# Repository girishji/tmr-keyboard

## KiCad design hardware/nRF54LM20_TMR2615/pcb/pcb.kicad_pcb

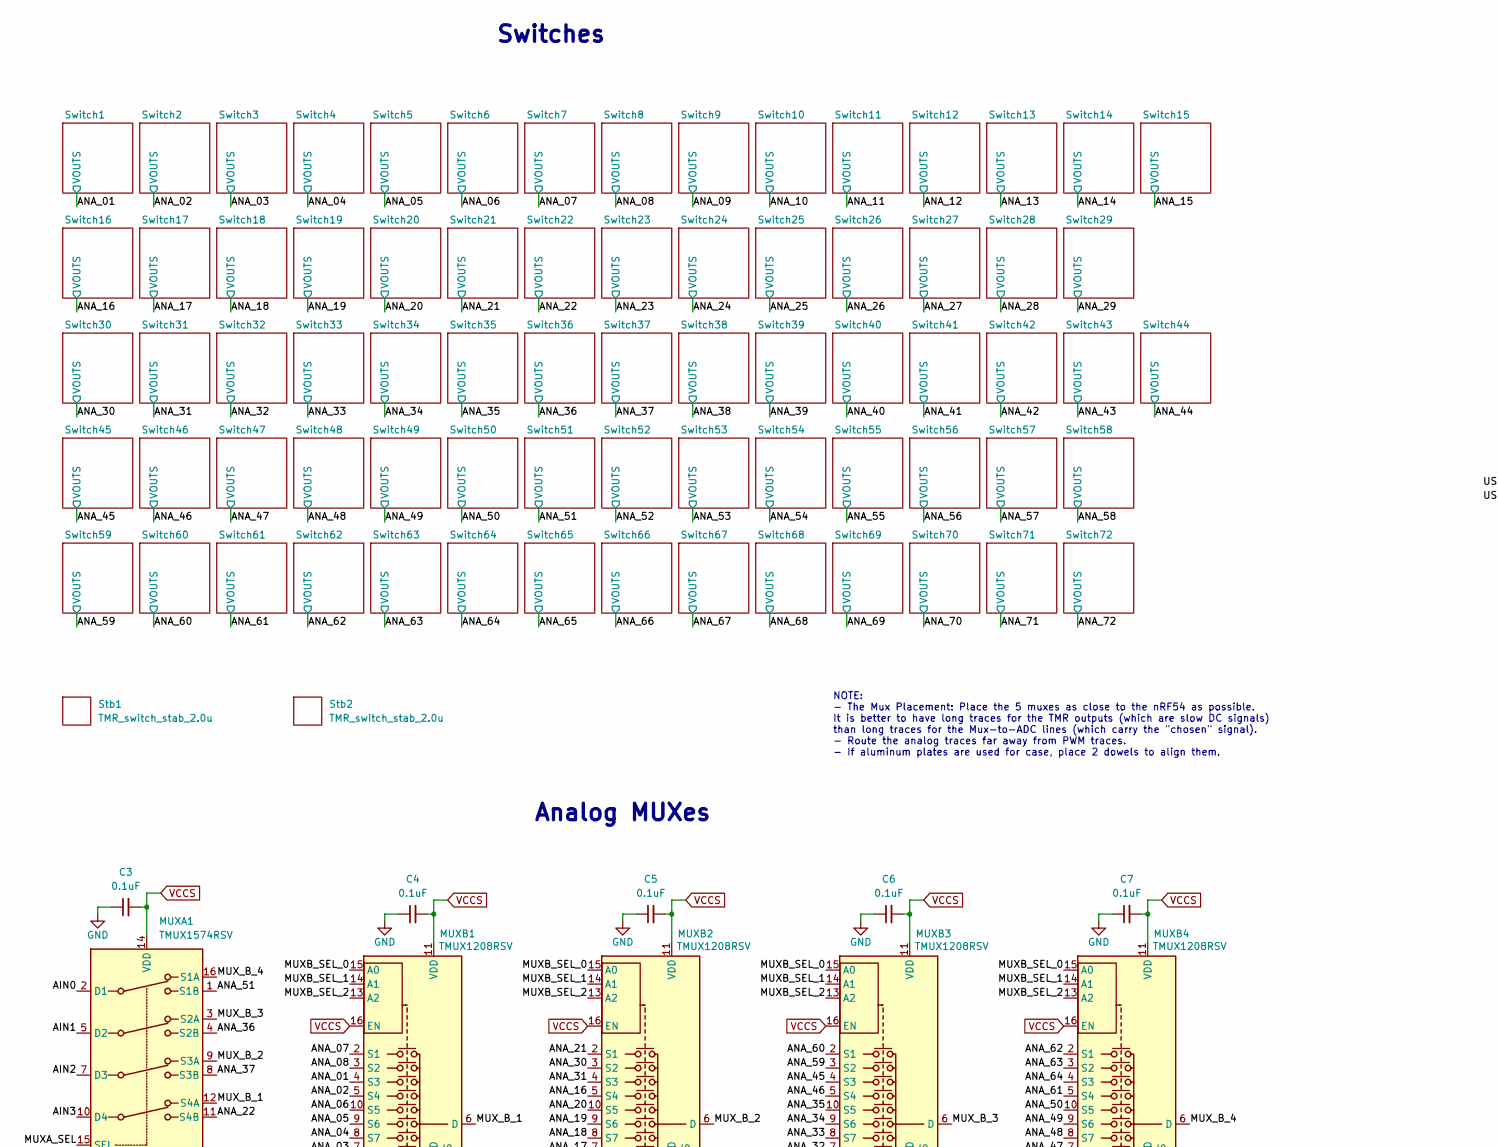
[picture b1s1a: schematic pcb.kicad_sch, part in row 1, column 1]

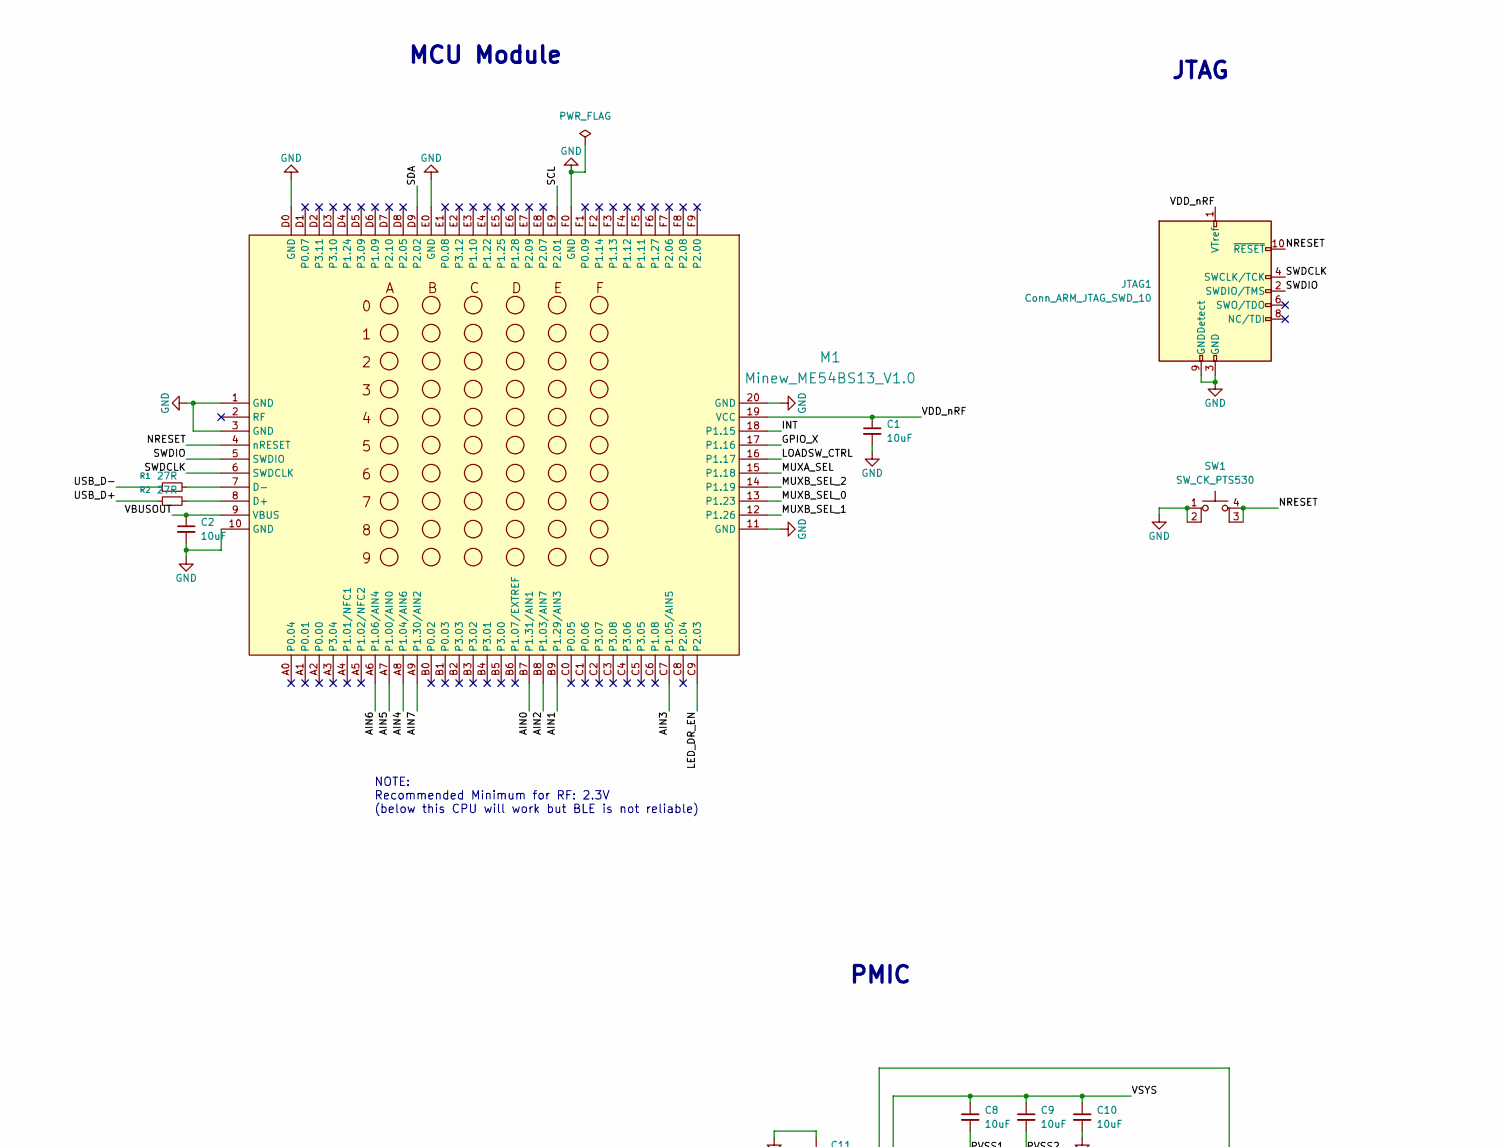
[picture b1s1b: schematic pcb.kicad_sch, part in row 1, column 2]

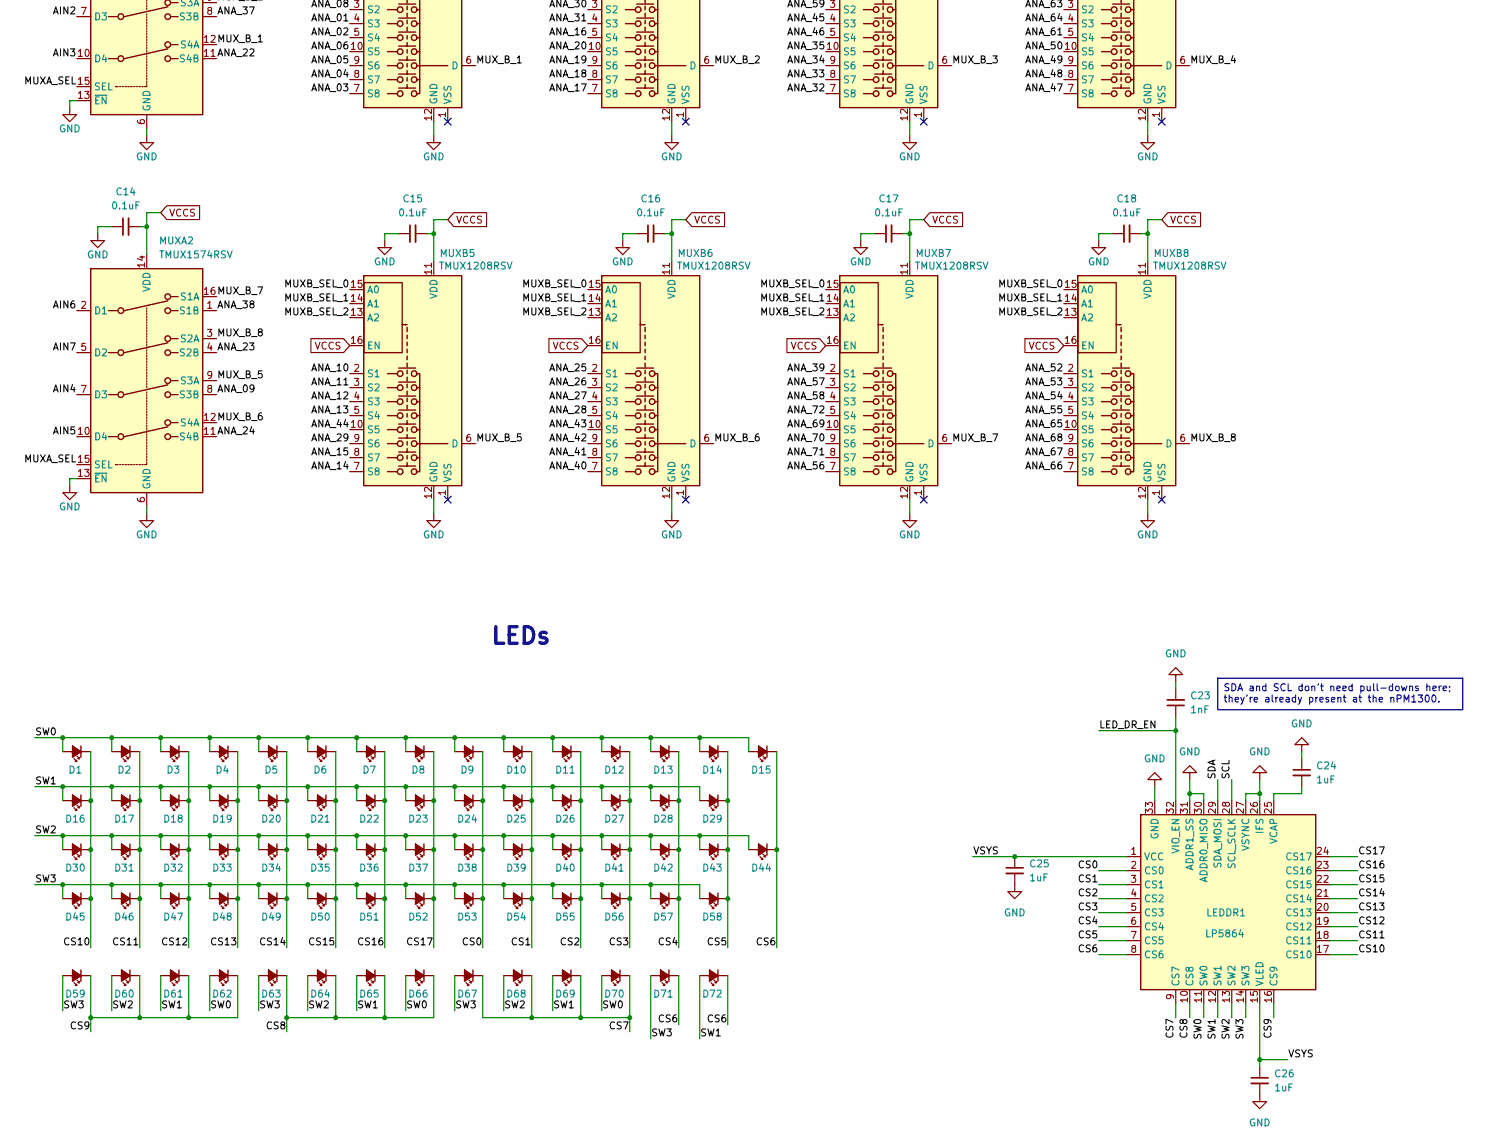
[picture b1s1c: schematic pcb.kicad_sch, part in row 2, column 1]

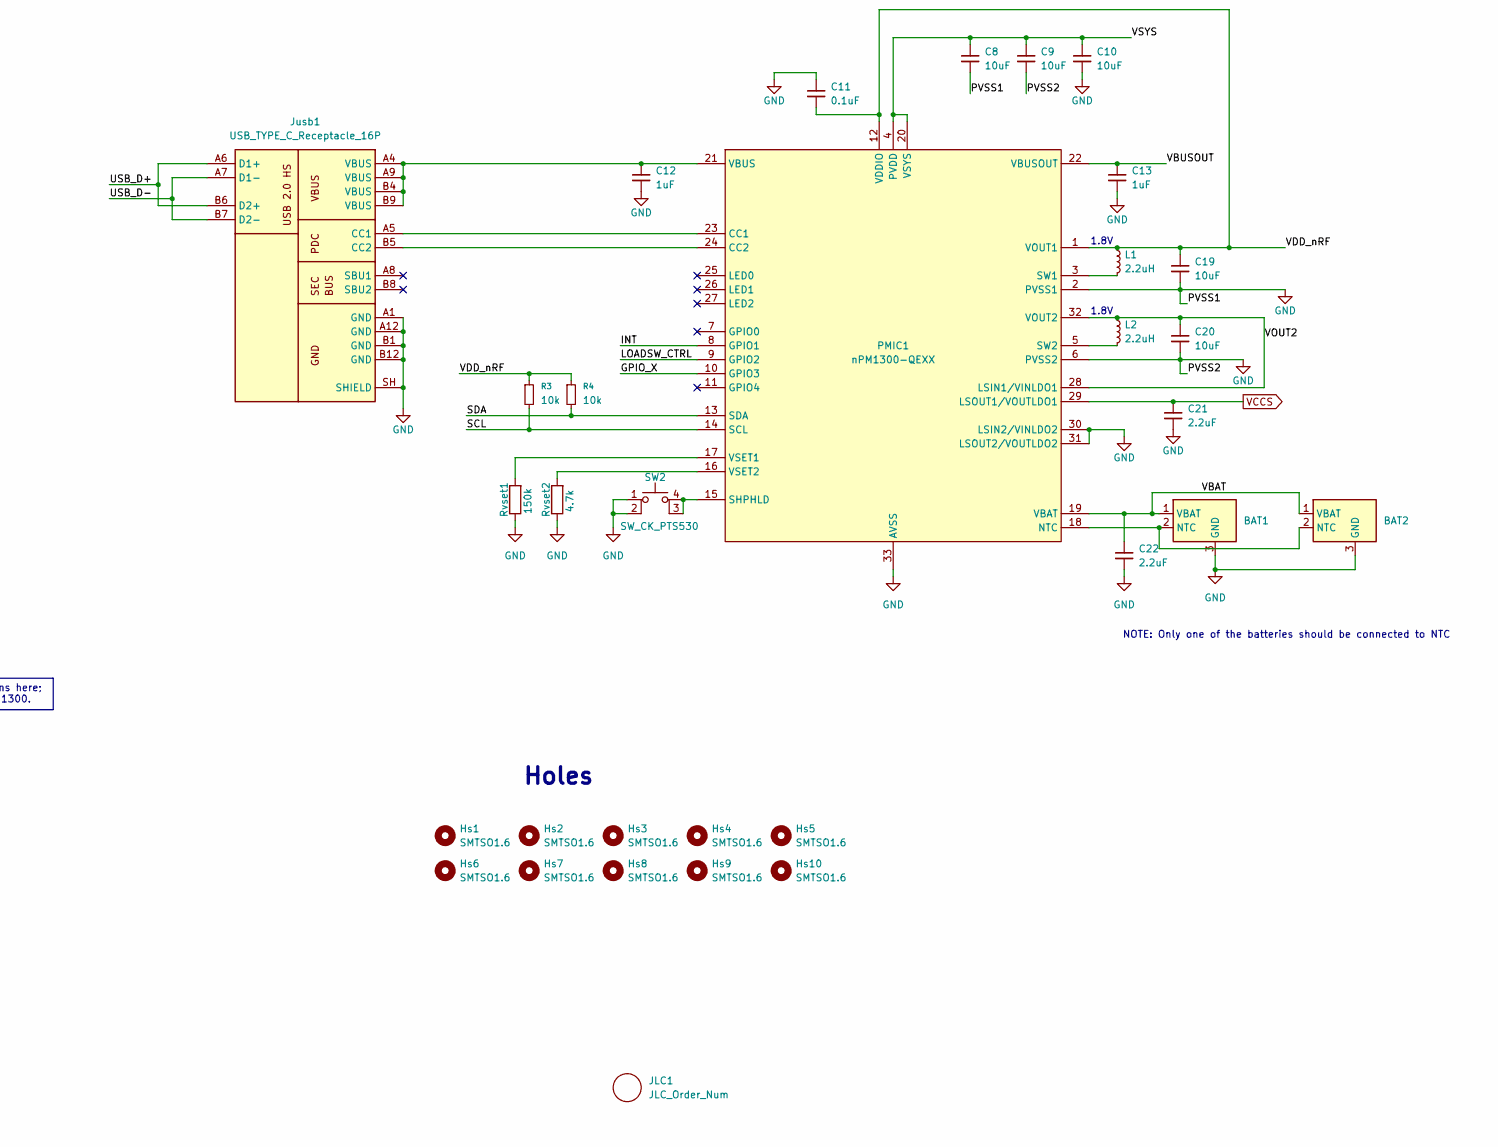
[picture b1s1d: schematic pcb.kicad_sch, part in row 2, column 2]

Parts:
BAT1, BAT2: PCB_Wire_Solder_3p_Connector
C1, C2, C8, C9, C10, C19, C20: 10uF; C_0603_1608Metric; LCSC C96446
C3, C4, C5, C6, C7, C11, C14, C15, C16, C17, C18: 0.1uF; C_0402_1005Metric; LCSC C129131
C12, C13, C24, C25, C26: 1uF; C_0402_1005Metric; LCSC C14445
C21, C22: 2.2uF; C_0603_1608Metric; LCSC C57895
C23: 1nF; C_0402_1005Metric; LCSC C710873
D1, D2, D3, D4, D5, D6, D7, D8, D9, D10, D11, D12, D13, D14, D15, D16, D17, D18, D19, D20, D21, D22, D23, D24, D25, D26, D27, D28, D29, D30, D31, D32, D33, D34, D35, D36, D37, D38, D39, D40, D41, D42, D43, D44, D45, D46, D47, D48, D49, D50, D51, D52, D53, D54, D55, D56, D57, D58, D59, D60, D61, D62, D63, D64, D65, D66, D67, D68, D69, D70, D71, D72: LED; LED_1206_3216Metric_ReverseMount_Hole2.1mm; LCSC C401114
Hs1, Hs2, Hs3, Hs4, Hs5, Hs6, Hs7, Hs8, Hs9, Hs10: SMTSO1.6; SMTSO_M1.6; LCSC C42924166
JLC1: JLC_Order_Num
JTAG1: Conn_ARM_JTAG_SWD_10; SAMTEC-CLP-105-02-X-D-A; LCSC C6882278
Jusb1: USB_TYPE_C_Receptacle_16P; USB_C_Receptacle_XKB_U262-16XN-4BVC11; MPN U262-161N-4BVC11; LCSC C319148
L1, L2: 2.2uH; L_Samsung_CIGT201610EH2R2MNE; LCSC C2049745
LEDDR1: LP5864; LP5864-VQFN-32-1EP_4x4mm_P0.4mm_EP2.8x2.8mm_ThermalVias; LCSC C5220564
M1: Minew_ME54BS13_V1.0; Minew_ME54BS13; LCSC C9900300294
MUXA1, MUXA2: TMUX1574RSV; UQFN-16_1.8x2.6mm_P0.4mm; LCSC C2673120
MUXB1, MUXB2, MUXB3, MUXB4, MUXB5, MUXB6, MUXB7, MUXB8: TMUX1208RSV; UQFN-16_1.8x2.6mm_P0.4mm; LCSC C2673274
PMIC1: nPM1300-QEXX; QFN-32-1EP_5x5mm_P0.5mm_EP3.6x3.6mm_ThermalVias; LCSC C25346894
R1, R2: 27R; R_0402_1005Metric; LCSC C25100
R3, R4: 10k; R_0402_1005Metric; LCSC C25744
Rvset1: 150k; R_0402_1005Metric; LCSC C25755
Rvset2: 4.7k; R_0402_1005Metric; LCSC C25900
SW1, SW2: SW_CK_PTS530; SW_CK_PTS530_4.5x4.5x0.55mm; LCSC C221860
Stb1, Stb2: TMR_switch_stab_2.0u; Stabilizer_Lowpro_2U

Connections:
/AIN0: M1.B7 (P1.31/AIN1), MUXA1.2 (D1)
/AIN1: M1.B9 (P1.29/AIN3), MUXA1.5 (D2)
/AIN2: M1.B8 (P1.03/AIN7), MUXA1.7 (D3)
/AIN3: M1.C7 (P1.05/AIN5), MUXA1.10 (D4)
/AIN4: M1.A8 (P1.04/AIN6), MUXA2.7 (D3)
/AIN5: M1.A7 (P1.00/AIN0), MUXA2.10 (D4)
/AIN6: M1.A6 (P1.06/AIN4), MUXA2.2 (D1)
/AIN7: M1.A9 (P1.30/AIN2), MUXA2.5 (D2)
/ANA_01: MUXB1.4 (S3); also elsewhere on the board
/ANA_02: MUXB1.5 (S4); also elsewhere on the board
/ANA_03: MUXB1.7 (S8); also elsewhere on the board
/ANA_04: MUXB1.8 (S7); also elsewhere on the board
/ANA_05: MUXB1.9 (S6); also elsewhere on the board
/ANA_06: MUXB1.10 (S5); also elsewhere on the board
/ANA_07: MUXB1.2 (S1); also elsewhere on the board
/ANA_08: MUXB1.3 (S2); also elsewhere on the board
/ANA_09: MUXA2.8 (S3B); also elsewhere on the board
/ANA_10: MUXB5.2 (S1); also elsewhere on the board
/ANA_11: MUXB5.3 (S2); also elsewhere on the board
/ANA_12: MUXB5.4 (S3); also elsewhere on the board
/ANA_13: MUXB5.5 (S4); also elsewhere on the board
/ANA_14: MUXB5.7 (S8); also elsewhere on the board
/ANA_15: MUXB5.8 (S7); also elsewhere on the board
/ANA_16: MUXB2.5 (S4); also elsewhere on the board
/ANA_17: MUXB2.7 (S8); also elsewhere on the board
/ANA_18: MUXB2.8 (S7); also elsewhere on the board
/ANA_19: MUXB2.9 (S6); also elsewhere on the board
/ANA_20: MUXB2.10 (S5); also elsewhere on the board
/ANA_21: MUXB2.2 (S1); also elsewhere on the board
/ANA_22: MUXA1.11 (S4B); also elsewhere on the board
/ANA_23: MUXA2.4 (S2B); also elsewhere on the board
/ANA_24: MUXA2.11 (S4B); also elsewhere on the board
/ANA_25: MUXB6.2 (S1); also elsewhere on the board
/ANA_26: MUXB6.3 (S2); also elsewhere on the board
/ANA_27: MUXB6.4 (S3); also elsewhere on the board
/ANA_28: MUXB6.5 (S4); also elsewhere on the board
/ANA_29: MUXB5.9 (S6); also elsewhere on the board
/ANA_30: MUXB2.3 (S2); also elsewhere on the board
/ANA_31: MUXB2.4 (S3); also elsewhere on the board
/ANA_32: MUXB3.7 (S8); also elsewhere on the board
/ANA_33: MUXB3.8 (S7); also elsewhere on the board
/ANA_34: MUXB3.9 (S6); also elsewhere on the board
/ANA_35: MUXB3.10 (S5); also elsewhere on the board
/ANA_36: MUXA1.4 (S2B); also elsewhere on the board
/ANA_37: MUXA1.8 (S3B); also elsewhere on the board
/ANA_38: MUXA2.1 (S1B); also elsewhere on the board
/ANA_39: MUXB7.2 (S1); also elsewhere on the board
/ANA_40: MUXB6.7 (S8); also elsewhere on the board
/ANA_41: MUXB6.8 (S7); also elsewhere on the board
/ANA_42: MUXB6.9 (S6); also elsewhere on the board
/ANA_43: MUXB6.10 (S5); also elsewhere on the board
/ANA_44: MUXB5.10 (S5); also elsewhere on the board
/ANA_45: MUXB3.4 (S3); also elsewhere on the board
/ANA_46: MUXB3.5 (S4); also elsewhere on the board
/ANA_47: MUXB4.7 (S8); also elsewhere on the board
/ANA_48: MUXB4.8 (S7); also elsewhere on the board
/ANA_49: MUXB4.9 (S6); also elsewhere on the board
/ANA_50: MUXB4.10 (S5); also elsewhere on the board
/ANA_51: MUXA1.1 (S1B); also elsewhere on the board
/ANA_52: MUXB8.2 (S1); also elsewhere on the board
/ANA_53: MUXB8.3 (S2); also elsewhere on the board
/ANA_54: MUXB8.4 (S3); also elsewhere on the board
/ANA_55: MUXB8.5 (S4); also elsewhere on the board
/ANA_56: MUXB7.7 (S8); also elsewhere on the board
/ANA_57: MUXB7.3 (S2); also elsewhere on the board
/ANA_58: MUXB7.4 (S3); also elsewhere on the board
/ANA_59: MUXB3.3 (S2); also elsewhere on the board
/ANA_60: MUXB3.2 (S1); also elsewhere on the board
/ANA_61: MUXB4.5 (S4); also elsewhere on the board
/ANA_62: MUXB4.2 (S1); also elsewhere on the board
/ANA_63: MUXB4.3 (S2); also elsewhere on the board
/ANA_64: MUXB4.4 (S3); also elsewhere on the board
/ANA_65: MUXB8.10 (S5); also elsewhere on the board
/ANA_66: MUXB8.7 (S8); also elsewhere on the board
/ANA_67: MUXB8.8 (S7); also elsewhere on the board
/ANA_68: MUXB8.9 (S6); also elsewhere on the board
/ANA_69: MUXB7.10 (S5); also elsewhere on the board
/ANA_70: MUXB7.9 (S6); also elsewhere on the board
/ANA_71: MUXB7.8 (S7); also elsewhere on the board
/ANA_72: MUXB7.5 (S4); also elsewhere on the board
/CS0: D9.1 (K), D24.1 (K), D38.1 (K), D53.1 (K), LEDDR1.2 (CS0)
/CS1: D10.1 (K), D25.1 (K), D39.1 (K), D54.1 (K), LEDDR1.3 (CS1)
/CS2: D11.1 (K), D26.1 (K), D40.1 (K), D55.1 (K), LEDDR1.4 (CS2)
/CS3: D12.1 (K), D27.1 (K), D41.1 (K), D56.1 (K), LEDDR1.5 (CS3)
/CS4: D13.1 (K), D28.1 (K), D42.1 (K), D57.1 (K), LEDDR1.6 (CS4)
/CS5: D14.1 (K), D29.1 (K), D43.1 (K), D58.1 (K), LEDDR1.7 (CS5)
/CS6: D15.1 (K), D44.1 (K), D71.1 (K), D72.1 (K), LEDDR1.8 (CS6)
/CS7: D67.1 (K), D68.1 (K), D69.1 (K), D70.1 (K), LEDDR1.9 (CS7)
/CS8: D63.1 (K), D64.1 (K), D65.1 (K), D66.1 (K), LEDDR1.10 (CS8)
/CS9: D59.1 (K), D60.1 (K), D61.1 (K), D62.1 (K), LEDDR1.16 (CS9)
/CS10: D1.1 (K), D16.1 (K), D30.1 (K), D45.1 (K), LEDDR1.17 (CS10)
/CS11: D2.1 (K), D17.1 (K), D31.1 (K), D46.1 (K), LEDDR1.18 (CS11)
/CS12: D3.1 (K), D18.1 (K), D32.1 (K), D47.1 (K), LEDDR1.19 (CS12)
/CS13: D4.1 (K), D19.1 (K), D33.1 (K), D48.1 (K), LEDDR1.20 (CS13)
/CS14: D5.1 (K), D20.1 (K), D34.1 (K), D49.1 (K), LEDDR1.21 (CS14)
/CS15: D6.1 (K), D21.1 (K), D35.1 (K), D50.1 (K), LEDDR1.22 (CS15)
/CS16: D7.1 (K), D22.1 (K), D36.1 (K), D51.1 (K), LEDDR1.23 (CS16)
/CS17: D8.1 (K), D23.1 (K), D37.1 (K), D52.1 (K), LEDDR1.24 (CS17)
/GPIO_X: M1.17 (P1.16), PMIC1.10 (GPIO3)
/INT: M1.18 (P1.15), PMIC1.8 (GPIO1)
/LED_DR_EN: C23.1, LEDDR1.32 (VIO_EN), M1.C9 (P2.03)
/LOADSW_CTRL: M1.16 (P1.17), PMIC1.9 (GPIO2)
/MUXA_SEL: M1.15 (P1.18), MUXA1.15 (SEL), MUXA2.15 (SEL)
/MUXB_SEL_0: M1.13 (P1.23), MUXB1.15 (A0), MUXB2.15 (A0), MUXB3.15 (A0), MUXB4.15 (A0), MUXB5.15 (A0), MUXB6.15 (A0), MUXB7.15 (A0), MUXB8.15 (A0)
/MUXB_SEL_1: M1.12 (P1.26), MUXB1.14 (A1), MUXB2.14 (A1), MUXB3.14 (A1), MUXB4.14 (A1), MUXB5.14 (A1), MUXB6.14 (A1), MUXB7.14 (A1), MUXB8.14 (A1)
/MUXB_SEL_2: M1.14 (P1.19), MUXB1.13 (A2), MUXB2.13 (A2), MUXB3.13 (A2), MUXB4.13 (A2), MUXB5.13 (A2), MUXB6.13 (A2), MUXB7.13 (A2), MUXB8.13 (A2)
/MUX_B_1: MUXA1.12 (S4A), MUXB1.6 (D)
/MUX_B_2: MUXA1.9 (S3A), MUXB2.6 (D)
/MUX_B_3: MUXA1.3 (S2A), MUXB3.6 (D)
/MUX_B_4: MUXA1.16 (S1A), MUXB4.6 (D)
/MUX_B_5: MUXA2.9 (S3A), MUXB5.6 (D)
/MUX_B_6: MUXA2.12 (S4A), MUXB6.6 (D)
/MUX_B_7: MUXA2.16 (S1A), MUXB7.6 (D)
/MUX_B_8: MUXA2.3 (S2A), MUXB8.6 (D)
/NRESET: JTAG1.10 (~RESET), M1.4 (nRESET), SW1.3 (K), SW1.4 (A)
/SCL: LEDDR1.28 (SCL_SCLK), M1.E9 (P2.01), PMIC1.14 (SCL), R3.2
/SDA: LEDDR1.29 (SDA_MOSI), M1.D9 (P2.02), PMIC1.13 (SDA), R4.2
/SW0: D1.2 (A), D2.2 (A), D3.2 (A), D4.2 (A), D5.2 (A), D6.2 (A), D7.2 (A), D8.2 (A), D9.2 (A), D10.2 (A), D11.2 (A), D12.2 (A), D13.2 (A), D14.2 (A), D15.2 (A), D62.2 (A), D66.2 (A), D70.2 (A), LEDDR1.11 (SW0)
/SW1: D16.2 (A), D17.2 (A), D18.2 (A), D19.2 (A), D20.2 (A), D21.2 (A), D22.2 (A), D23.2 (A), D24.2 (A), D25.2 (A), D26.2 (A), D27.2 (A), D28.2 (A), D29.2 (A), D61.2 (A), D65.2 (A), D69.2 (A), D72.2 (A), LEDDR1.12 (SW1)
/SW2: D30.2 (A), D31.2 (A), D32.2 (A), D33.2 (A), D34.2 (A), D35.2 (A), D36.2 (A), D37.2 (A), D38.2 (A), D39.2 (A), D40.2 (A), D41.2 (A), D42.2 (A), D43.2 (A), D44.2 (A), D60.2 (A), D64.2 (A), D68.2 (A), LEDDR1.13 (SW2)
/SW3: D45.2 (A), D46.2 (A), D47.2 (A), D48.2 (A), D49.2 (A), D50.2 (A), D51.2 (A), D52.2 (A), D53.2 (A), D54.2 (A), D55.2 (A), D56.2 (A), D57.2 (A), D58.2 (A), D59.2 (A), D63.2 (A), D67.2 (A), D71.2 (A), LEDDR1.14 (SW3)
/SWDCLK: JTAG1.4 (SWCLK/TCK), M1.6 (SWDCLK)
/SWDIO: JTAG1.2 (SWDIO/TMS), M1.5 (SWDIO)
/USB_D+: Jusb1.A6 (D1+), Jusb1.B6 (D2+), R2.1
/USB_D-: Jusb1.A7 (D1-), Jusb1.B7 (D2-), R1.1
/VBAT: BAT1.1 (VBAT), BAT2.1 (VBAT), C22.1, PMIC1.19 (VBAT)
/VBUSOUT: C2.1, C13.1, M1.9 (VBUS), PMIC1.22 (VBUSOUT)
/VDD_nRF: C1.1, C11.2, C19.1, JTAG1.1 (VTref), L1.1, M1.19 (VCC), PMIC1.1 (VOUT1), PMIC1.12 (VDDIO), R3.1, R4.1
/VOUT2: C20.1, L2.1, PMIC1.28 (LSIN1/VINLDO1), PMIC1.32 (VOUT2)
/VSYS: C8.1, C9.1, C10.1, C25.1, C26.1, LEDDR1.1 (VCC), LEDDR1.15 (VLED), PMIC1.4 (PVDD), PMIC1.20 (VSYS)
GND: BAT1.3 (GND), BAT2.3 (GND), C1.2, C2.2, C3.1, C4.1, C5.1, C6.1, C7.1, C8.2, C9.2, C10.2, C11.1, C12.2, C13.2, C14.1, C15.1, C16.1, C17.1, C18.1, C19.2, C20.2, C21.2, C22.2, C23.2, C24.1, C25.2, C26.2, JTAG1.3 (GND), JTAG1.5 (GND), JTAG1.9 (GNDDetect), Jusb1.A1 (GND), Jusb1.A12 (GND), Jusb1.B1 (GND), Jusb1.B12 (GND), Jusb1.SH (SHIELD), LEDDR1.26 (IFS), LEDDR1.27 (VSYNC), LEDDR1.30 (ADDR0_MISO), LEDDR1.31 (ADDR1_SS), LEDDR1.33 (GND), M1.1 (GND), M1.3 (GND), M1.10 (GND), M1.11 (GND), M1.20 (GND), M1.D0 (GND), M1.E0 (GND), M1.F0 (GND), MUXA1.6 (GND), MUXA1.13 (~EN), MUXA2.6 (GND), MUXA2.13 (~EN), MUXB1.12 (GND), MUXB2.12 (GND), MUXB3.12 (GND), MUXB4.12 (GND), MUXB5.12 (GND), MUXB6.12 (GND), MUXB7.12 (GND), MUXB8.12 (GND), PMIC1.2 (PVSS1), PMIC1.6 (PVSS2), PMIC1.30 (LSIN2/VINLDO2), PMIC1.31 (LSOUT2/VOUTLDO2), PMIC1.33 (AVSS), Rvset1.1, Rvset2.1, SW1.1, SW1.2, SW2.1, SW2.2; also elsewhere on the board
unnamed: BAT1.2 (NTC), BAT2.2 (NTC), PMIC1.18 (NTC)
unnamed: Jusb1.A5 (CC1), PMIC1.23 (CC1)
unnamed: Jusb1.B5 (CC2), PMIC1.24 (CC2)
unnamed: C24.2, LEDDR1.25 (VCAP)
unnamed: M1.8 (D+), R2.2
unnamed: M1.7 (D-), R1.2
unnamed: PMIC1.15 (SHPHLD), SW2.3 (K), SW2.4 (A)
unnamed: L1.2, PMIC1.3 (SW1)
unnamed: L2.2, PMIC1.5 (SW2)
unnamed: C12.1, Jusb1.A4 (VBUS), Jusb1.A9 (VBUS), Jusb1.B4 (VBUS), Jusb1.B9 (VBUS), PMIC1.21 (VBUS)
unnamed: PMIC1.17 (VSET1), Rvset1.2
unnamed: PMIC1.16 (VSET2), Rvset2.2
VCCS: C3.2, C4.2, C5.2, C6.2, C7.2, C14.2, C15.2, C16.2, C17.2, C18.2, C21.1, MUXA1.14 (VDD), MUXA2.14 (VDD), MUXB1.11 (VDD), MUXB1.16 (EN), MUXB2.11 (VDD), MUXB2.16 (EN), MUXB3.11 (VDD), MUXB3.16 (EN), MUXB4.11 (VDD), MUXB4.16 (EN), MUXB5.11 (VDD), MUXB5.16 (EN), MUXB6.11 (VDD), MUXB6.16 (EN), MUXB7.11 (VDD), MUXB7.16 (EN), MUXB8.11 (VDD), MUXB8.16 (EN), PMIC1.29 (LSOUT1/VOUTLDO1); also elsewhere on the board

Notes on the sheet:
Holes
MCU Module
NOTE: Only one of the batteries should be connected to NTC
NOTE: Recommended Minimum for RF: 2.3V (below this CPU will work but BLE is not reliable)
1.8V
Analog MUXes
JTAG
LEDs
PMIC
NOTE: - The Mux Placement: Place the 5 muxes as close to the nRF54 as possible. It is better to have long traces for the TMR outputs (which are slow DC signals) than long traces for the Mux-to-ADC lines (which carry the "chosen" signal). - Route the analog traces far away from PWM traces. - If alum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
Switches
SDA and SCL don't need pull-downs here; they're already present at the nPM1300.

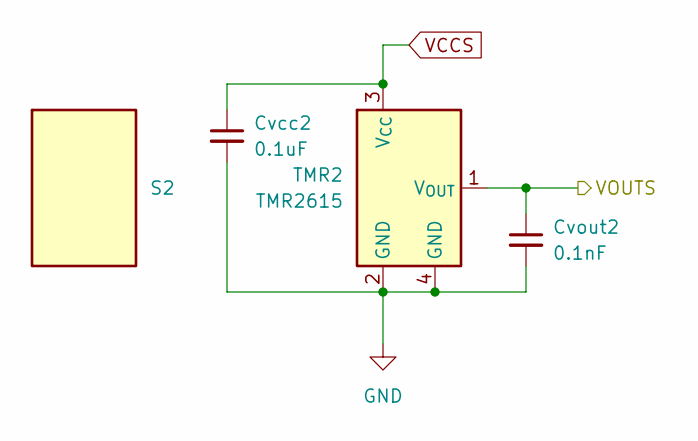
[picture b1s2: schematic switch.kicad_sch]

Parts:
Cvcc2: 0.1uF; C_0402_1005Metric_Cvcc; LCSC C129131
Cvout2: 0.1nF; C_0402_1005Metric_Cvout; LCSC C77177
S2: Switch; Kailh_gateron_sw_lowpro
TMR2: TMR2615; TMR2615-DFN-3L-1.6x1.6; LCSC C9900212297

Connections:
/ANA_02: Cvout2.1, TMR2.1 (V_{OUT}); also elsewhere on the board
GND: Cvcc2.2, Cvout2.2, TMR2.2 (GND), TMR2.4 (GND); also elsewhere on the board
VCCS: Cvcc2.1, TMR2.3 (V_{CC}); also elsewhere on the board

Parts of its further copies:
Cvcc1, Cvcc3, Cvcc4, Cvcc5, Cvcc6, Cvcc7, Cvcc8, Cvcc9, Cvcc10, Cvcc11, Cvcc12, Cvcc13, Cvcc14, Cvcc15, Cvcc16, Cvcc17, Cvcc18, Cvcc19, Cvcc20, Cvcc21, Cvcc22, Cvcc23, Cvcc24, Cvcc25, Cvcc26, Cvcc27, Cvcc28, Cvcc29, Cvcc30, Cvcc31, Cvcc32, Cvcc33, Cvcc34, Cvcc35, Cvcc36, Cvcc37, Cvcc38, Cvcc39, Cvcc40, Cvcc41, Cvcc42, Cvcc43, Cvcc44, Cvcc45, Cvcc46, Cvcc47, Cvcc48, Cvcc49, Cvcc50, Cvcc51, Cvcc52, Cvcc53, Cvcc54, Cvcc55, Cvcc56, Cvcc57, Cvcc58, Cvcc59, Cvcc60, Cvcc61, Cvcc62, Cvcc63, Cvcc64, Cvcc65, Cvcc66, Cvcc67, Cvcc68, Cvcc69, Cvcc70, Cvcc71, Cvcc72: 0.1uF; C_0402_1005Metric_Cvcc; LCSC C129131
Cvout1, Cvout3, Cvout4, Cvout5, Cvout6, Cvout7, Cvout8, Cvout9, Cvout10, Cvout11, Cvout12, Cvout13, Cvout14, Cvout15, Cvout16, Cvout17, Cvout18, Cvout19, Cvout20, Cvout21, Cvout22, Cvout23, Cvout24, Cvout25, Cvout26, Cvout27, Cvout28, Cvout29, Cvout30, Cvout31, Cvout32, Cvout33, Cvout34, Cvout35, Cvout36, Cvout37, Cvout38, Cvout39, Cvout40, Cvout41, Cvout42, Cvout43, Cvout44, Cvout45, Cvout46, Cvout47, Cvout48, Cvout49, Cvout50, Cvout51, Cvout52, Cvout53, Cvout54, Cvout55, Cvout56, Cvout57, Cvout58, Cvout59, Cvout60, Cvout61, Cvout62, Cvout63, Cvout64, Cvout65, Cvout66, Cvout67, Cvout68, Cvout69, Cvout70, Cvout71, Cvout72: 0.1nF; C_0402_1005Metric_Cvout; LCSC C77177
S1, S3, S4, S5, S6, S7, S8, S9, S10, S11, S12, S13, S14, S15, S16, S17, S18, S19, S20, S21, S22, S23, S24, S25, S26, S27, S28, S29, S30, S31, S32, S33, S34, S35, S36, S37, S38, S39, S40, S41, S42, S43, S44, S45, S46, S47, S48, S49, S50, S51, S52, S53, S54, S55, S56, S57, S58, S59, S60, S61, S62, S63, S64, S65, S66, S67, S68, S69, S70, S71, S72: Switch; Kailh_gateron_sw_lowpro
TMR1, TMR3, TMR4, TMR5, TMR6, TMR7, TMR8, TMR9, TMR10, TMR11, TMR12, TMR13, TMR14, TMR15, TMR16, TMR17, TMR18, TMR19, TMR20, TMR21, TMR22, TMR23, TMR24, TMR25, TMR26, TMR27, TMR28, TMR29, TMR30, TMR31, TMR32, TMR33, TMR34, TMR35, TMR36, TMR37, TMR38, TMR39, TMR40, TMR41, TMR42, TMR43, TMR44, TMR45, TMR46, TMR47, TMR48, TMR49, TMR50, TMR51, TMR52, TMR53, TMR54, TMR55, TMR56, TMR57, TMR58, TMR59, TMR60, TMR61, TMR62, TMR63, TMR64, TMR65, TMR66, TMR67, TMR68, TMR69, TMR70, TMR71, TMR72: TMR2615; TMR2615-DFN-3L-1.6x1.6; LCSC C9900212297

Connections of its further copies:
/ANA_01: Cvout1.1, TMR1.1 (V_{OUT}); also elsewhere on the board
/ANA_03: Cvout3.1, TMR3.1 (V_{OUT}); also elsewhere on the board
/ANA_04: Cvout4.1, TMR4.1 (V_{OUT}); also elsewhere on the board
/ANA_05: Cvout5.1, TMR5.1 (V_{OUT}); also elsewhere on the board
/ANA_06: Cvout6.1, TMR6.1 (V_{OUT}); also elsewhere on the board
/ANA_07: Cvout7.1, TMR7.1 (V_{OUT}); also elsewhere on the board
/ANA_08: Cvout8.1, TMR8.1 (V_{OUT}); also elsewhere on the board
/ANA_09: Cvout9.1, TMR9.1 (V_{OUT}); also elsewhere on the board
/ANA_10: Cvout10.1, TMR10.1 (V_{OUT}); also elsewhere on the board
/ANA_11: Cvout11.1, TMR11.1 (V_{OUT}); also elsewhere on the board
/ANA_12: Cvout12.1, TMR12.1 (V_{OUT}); also elsewhere on the board
/ANA_13: Cvout13.1, TMR13.1 (V_{OUT}); also elsewhere on the board
/ANA_14: Cvout14.1, TMR14.1 (V_{OUT}); also elsewhere on the board
/ANA_15: Cvout15.1, TMR15.1 (V_{OUT}); also elsewhere on the board
/ANA_16: Cvout16.1, TMR16.1 (V_{OUT}); also elsewhere on the board
/ANA_17: Cvout17.1, TMR17.1 (V_{OUT}); also elsewhere on the board
/ANA_18: Cvout18.1, TMR18.1 (V_{OUT}); also elsewhere on the board
/ANA_19: Cvout19.1, TMR19.1 (V_{OUT}); also elsewhere on the board
/ANA_20: Cvout20.1, TMR20.1 (V_{OUT}); also elsewhere on the board
/ANA_21: Cvout21.1, TMR21.1 (V_{OUT}); also elsewhere on the board
/ANA_22: Cvout22.1, TMR22.1 (V_{OUT}); also elsewhere on the board
/ANA_23: Cvout23.1, TMR23.1 (V_{OUT}); also elsewhere on the board
/ANA_24: Cvout24.1, TMR24.1 (V_{OUT}); also elsewhere on the board
/ANA_25: Cvout25.1, TMR25.1 (V_{OUT}); also elsewhere on the board
/ANA_26: Cvout26.1, TMR26.1 (V_{OUT}); also elsewhere on the board
/ANA_27: Cvout27.1, TMR27.1 (V_{OUT}); also elsewhere on the board
/ANA_28: Cvout28.1, TMR28.1 (V_{OUT}); also elsewhere on the board
/ANA_29: Cvout29.1, TMR29.1 (V_{OUT}); also elsewhere on the board
/ANA_30: Cvout30.1, TMR30.1 (V_{OUT}); also elsewhere on the board
/ANA_31: Cvout31.1, TMR31.1 (V_{OUT}); also elsewhere on the board
/ANA_32: Cvout32.1, TMR32.1 (V_{OUT}); also elsewhere on the board
/ANA_33: Cvout33.1, TMR33.1 (V_{OUT}); also elsewhere on the board
/ANA_34: Cvout34.1, TMR34.1 (V_{OUT}); also elsewhere on the board
/ANA_35: Cvout35.1, TMR35.1 (V_{OUT}); also elsewhere on the board
/ANA_36: Cvout36.1, TMR36.1 (V_{OUT}); also elsewhere on the board
/ANA_37: Cvout37.1, TMR37.1 (V_{OUT}); also elsewhere on the board
/ANA_38: Cvout38.1, TMR38.1 (V_{OUT}); also elsewhere on the board
/ANA_39: Cvout39.1, TMR39.1 (V_{OUT}); also elsewhere on the board
/ANA_40: Cvout40.1, TMR40.1 (V_{OUT}); also elsewhere on the board
/ANA_41: Cvout41.1, TMR41.1 (V_{OUT}); also elsewhere on the board
/ANA_42: Cvout42.1, TMR42.1 (V_{OUT}); also elsewhere on the board
/ANA_43: Cvout43.1, TMR43.1 (V_{OUT}); also elsewhere on the board
/ANA_44: Cvout44.1, TMR44.1 (V_{OUT}); also elsewhere on the board
/ANA_45: Cvout45.1, TMR45.1 (V_{OUT}); also elsewhere on the board
/ANA_46: Cvout46.1, TMR46.1 (V_{OUT}); also elsewhere on the board
/ANA_47: Cvout47.1, TMR47.1 (V_{OUT}); also elsewhere on the board
/ANA_48: Cvout48.1, TMR48.1 (V_{OUT}); also elsewhere on the board
/ANA_49: Cvout49.1, TMR49.1 (V_{OUT}); also elsewhere on the board
/ANA_50: Cvout50.1, TMR50.1 (V_{OUT}); also elsewhere on the board
/ANA_51: Cvout51.1, TMR51.1 (V_{OUT}); also elsewhere on the board
/ANA_52: Cvout52.1, TMR52.1 (V_{OUT}); also elsewhere on the board
/ANA_53: Cvout53.1, TMR53.1 (V_{OUT}); also elsewhere on the board
/ANA_54: Cvout54.1, TMR54.1 (V_{OUT}); also elsewhere on the board
/ANA_55: Cvout55.1, TMR55.1 (V_{OUT}); also elsewhere on the board
/ANA_56: Cvout56.1, TMR56.1 (V_{OUT}); also elsewhere on the board
/ANA_57: Cvout57.1, TMR57.1 (V_{OUT}); also elsewhere on the board
/ANA_58: Cvout58.1, TMR58.1 (V_{OUT}); also elsewhere on the board
/ANA_59: Cvout59.1, TMR59.1 (V_{OUT}); also elsewhere on the board
/ANA_60: Cvout60.1, TMR60.1 (V_{OUT}); also elsewhere on the board
/ANA_61: Cvout61.1, TMR61.1 (V_{OUT}); also elsewhere on the board
/ANA_62: Cvout62.1, TMR62.1 (V_{OUT}); also elsewhere on the board
/ANA_63: Cvout63.1, TMR63.1 (V_{OUT}); also elsewhere on the board
/ANA_64: Cvout64.1, TMR64.1 (V_{OUT}); also elsewhere on the board
/ANA_65: Cvout65.1, TMR65.1 (V_{OUT}); also elsewhere on the board
/ANA_66: Cvout66.1, TMR66.1 (V_{OUT}); also elsewhere on the board
/ANA_67: Cvout67.1, TMR67.1 (V_{OUT}); also elsewhere on the board
/ANA_68: Cvout68.1, TMR68.1 (V_{OUT}); also elsewhere on the board
/ANA_69: Cvout69.1, TMR69.1 (V_{OUT}); also elsewhere on the board
/ANA_70: Cvout70.1, TMR70.1 (V_{OUT}); also elsewhere on the board
/ANA_71: Cvout71.1, TMR71.1 (V_{OUT}); also elsewhere on the board
/ANA_72: Cvout72.1, TMR72.1 (V_{OUT}); also elsewhere on the board
GND: Cvcc1.2, Cvcc3.2, Cvcc4.2, Cvcc5.2, Cvcc6.2, Cvcc7.2, Cvcc8.2, Cvcc9.2, Cvcc10.2, Cvcc11.2, Cvcc12.2, Cvcc13.2, Cvcc14.2, Cvcc15.2, Cvcc16.2, Cvcc17.2, Cvcc18.2, Cvcc19.2, Cvcc20.2, Cvcc21.2, Cvcc22.2, Cvcc23.2, Cvcc24.2, Cvcc25.2, Cvcc26.2, Cvcc27.2, Cvcc28.2, Cvcc29.2, Cvcc30.2, Cvcc31.2, Cvcc32.2, Cvcc33.2, Cvcc34.2, Cvcc35.2, Cvcc36.2, Cvcc37.2, Cvcc38.2, Cvcc39.2, Cvcc40.2, Cvcc41.2, Cvcc42.2, Cvcc43.2, Cvcc44.2, Cvcc45.2, Cvcc46.2, Cvcc47.2, Cvcc48.2, Cvcc49.2, Cvcc50.2, Cvcc51.2, Cvcc52.2, Cvcc53.2, Cvcc54.2, Cvcc55.2, Cvcc56.2, Cvcc57.2, Cvcc58.2, Cvcc59.2, Cvcc60.2, Cvcc61.2, Cvcc62.2, Cvcc63.2, Cvcc64.2, Cvcc65.2, Cvcc66.2, Cvcc67.2, Cvcc68.2, Cvcc69.2, Cvcc70.2, Cvcc71.2, Cvcc72.2, Cvout1.2, Cvout3.2, Cvout4.2, Cvout5.2, Cvout6.2, Cvout7.2, Cvout8.2, Cvout9.2, Cvout10.2, Cvout11.2, Cvout12.2, Cvout13.2, Cvout14.2, Cvout15.2, Cvout16.2, Cvout17.2, Cvout18.2, Cvout19.2, Cvout20.2, Cvout21.2, Cvout22.2, Cvout23.2, Cvout24.2, Cvout25.2, Cvout26.2, Cvout27.2, Cvout28.2, Cvout29.2, Cvout30.2, Cvout31.2, Cvout32.2, Cvout33.2, Cvout34.2, Cvout35.2, Cvout36.2, Cvout37.2, Cvout38.2, Cvout39.2, Cvout40.2, Cvout41.2, Cvout42.2, Cvout43.2, Cvout44.2, Cvout45.2, Cvout46.2, Cvout47.2, Cvout48.2, Cvout49.2, Cvout50.2, Cvout51.2, Cvout52.2, Cvout53.2, Cvout54.2, Cvout55.2, Cvout56.2, Cvout57.2, Cvout58.2, Cvout59.2, Cvout60.2, Cvout61.2, Cvout62.2, Cvout63.2, Cvout64.2, Cvout65.2, Cvout66.2, Cvout67.2, Cvout68.2, Cvout69.2, Cvout70.2, Cvout71.2, Cvout72.2, TMR1.2 (GND), TMR1.4 (GND), TMR3.2 (GND), TMR3.4 (GND), TMR4.2 (GND), TMR4.4 (GND), TMR5.2 (GND), TMR5.4 (GND), TMR6.2 (GND), TMR6.4 (GND), TMR7.2 (GND), TMR7.4 (GND), TMR8.2 (GND), TMR8.4 (GND), TMR9.2 (GND), TMR9.4 (GND), TMR10.2 (GND), TMR10.4 (GND), TMR11.2 (GND), TMR11.4 (GND), TMR12.2 (GND), TMR12.4 (GND), TMR13.2 (GND), TMR13.4 (GND), TMR14.2 (GND), TMR14.4 (GND), TMR15.2 (GND), TMR15.4 (GND), TMR16.2 (GND), TMR16.4 (GND), TMR17.2 (GND), TMR17.4 (GND), TMR18.2 (GND), TMR18.4 (GND), TMR19.2 (GND), TMR19.4 (GND), TMR20.2 (GND), TMR20.4 (GND), TMR21.2 (GND), TMR21.4 (GND), TMR22.2 (GND), TMR22.4 (GND), TMR23.2 (GND), TMR23.4 (GND), TMR24.2 (GND), TMR24.4 (GND), TMR25.2 (GND), TMR25.4 (GND), TMR26.2 (GND), TMR26.4 (GND), TMR27.2 (GND), TMR27.4 (GND), TMR28.2 (GND), TMR28.4 (GND), TMR29.2 (GND), TMR29.4 (GND), TMR30.2 (GND), TMR30.4 (GND), TMR31.2 (GND), TMR31.4 (GND), TMR32.2 (GND), TMR32.4 (GND), TMR33.2 (GND), TMR33.4 (GND), TMR34.2 (GND), TMR34.4 (GND), TMR35.2 (GND), TMR35.4 (GND), TMR36.2 (GND), TMR36.4 (GND), TMR37.2 (GND), TMR37.4 (GND), TMR38.2 (GND), TMR38.4 (GND), TMR39.2 (GND), TMR39.4 (GND), TMR40.2 (GND), TMR40.4 (GND), TMR41.2 (GND), TMR41.4 (GND), TMR42.2 (GND), TMR42.4 (GND), TMR43.2 (GND), TMR43.4 (GND), TMR44.2 (GND), TMR44.4 (GND), TMR45.2 (GND), TMR45.4 (GND), TMR46.2 (GND), TMR46.4 (GND), TMR47.2 (GND), TMR47.4 (GND), TMR48.2 (GND), TMR48.4 (GND), TMR49.2 (GND), TMR49.4 (GND), TMR50.2 (GND), TMR50.4 (GND), TMR51.2 (GND), TMR51.4 (GND), TMR52.2 (GND), TMR52.4 (GND), TMR53.2 (GND), TMR53.4 (GND), TMR54.2 (GND), TMR54.4 (GND), TMR55.2 (GND), TMR55.4 (GND), TMR56.2 (GND), TMR56.4 (GND), TMR57.2 (GND), TMR57.4 (GND), TMR58.2 (GND), TMR58.4 (GND), TMR59.2 (GND), TMR59.4 (GND), TMR60.2 (GND), TMR60.4 (GND), TMR61.2 (GND), TMR61.4 (GND), TMR62.2 (GND), TMR62.4 (GND), TMR63.2 (GND), TMR63.4 (GND), TMR64.2 (GND), TMR64.4 (GND), TMR65.2 (GND), TMR65.4 (GND), TMR66.2 (GND), TMR66.4 (GND), TMR67.2 (GND), TMR67.4 (GND), TMR68.2 (GND), TMR68.4 (GND), TMR69.2 (GND), TMR69.4 (GND), TMR70.2 (GND), TMR70.4 (GND), TMR71.2 (GND), TMR71.4 (GND), TMR72.2 (GND), TMR72.4 (GND); also elsewhere on the board
VCCS: Cvcc1.1, Cvcc3.1, Cvcc4.1, Cvcc5.1, Cvcc6.1, Cvcc7.1, Cvcc8.1, Cvcc9.1, Cvcc10.1, Cvcc11.1, Cvcc12.1, Cvcc13.1, Cvcc14.1, Cvcc15.1, Cvcc16.1, Cvcc17.1, Cvcc18.1, Cvcc19.1, Cvcc20.1, Cvcc21.1, Cvcc22.1, Cvcc23.1, Cvcc24.1, Cvcc25.1, Cvcc26.1, Cvcc27.1, Cvcc28.1, Cvcc29.1, Cvcc30.1, Cvcc31.1, Cvcc32.1, Cvcc33.1, Cvcc34.1, Cvcc35.1, Cvcc36.1, Cvcc37.1, Cvcc38.1, Cvcc39.1, Cvcc40.1, Cvcc41.1, Cvcc42.1, Cvcc43.1, Cvcc44.1, Cvcc45.1, Cvcc46.1, Cvcc47.1, Cvcc48.1, Cvcc49.1, Cvcc50.1, Cvcc51.1, Cvcc52.1, Cvcc53.1, Cvcc54.1, Cvcc55.1, Cvcc56.1, Cvcc57.1, Cvcc58.1, Cvcc59.1, Cvcc60.1, Cvcc61.1, Cvcc62.1, Cvcc63.1, Cvcc64.1, Cvcc65.1, Cvcc66.1, Cvcc67.1, Cvcc68.1, Cvcc69.1, Cvcc70.1, Cvcc71.1, Cvcc72.1, TMR1.3 (V_{CC}), TMR3.3 (V_{CC}), TMR4.3 (V_{CC}), TMR5.3 (V_{CC}), TMR6.3 (V_{CC}), TMR7.3 (V_{CC}), TMR8.3 (V_{CC}), TMR9.3 (V_{CC}), TMR10.3 (V_{CC}), TMR11.3 (V_{CC}), TMR12.3 (V_{CC}), TMR13.3 (V_{CC}), TMR14.3 (V_{CC}), TMR15.3 (V_{CC}), TMR16.3 (V_{CC}), TMR17.3 (V_{CC}), TMR18.3 (V_{CC}), TMR19.3 (V_{CC}), TMR20.3 (V_{CC}), TMR21.3 (V_{CC}), TMR22.3 (V_{CC}), TMR23.3 (V_{CC}), TMR24.3 (V_{CC}), TMR25.3 (V_{CC}), TMR26.3 (V_{CC}), TMR27.3 (V_{CC}), TMR28.3 (V_{CC}), TMR29.3 (V_{CC}), TMR30.3 (V_{CC}), TMR31.3 (V_{CC}), TMR32.3 (V_{CC}), TMR33.3 (V_{CC}), TMR34.3 (V_{CC}), TMR35.3 (V_{CC}), TMR36.3 (V_{CC}), TMR37.3 (V_{CC}), TMR38.3 (V_{CC}), TMR39.3 (V_{CC}), TMR40.3 (V_{CC}), TMR41.3 (V_{CC}), TMR42.3 (V_{CC}), TMR43.3 (V_{CC}), TMR44.3 (V_{CC}), TMR45.3 (V_{CC}), TMR46.3 (V_{CC}), TMR47.3 (V_{CC}), TMR48.3 (V_{CC}), TMR49.3 (V_{CC}), TMR50.3 (V_{CC}), TMR51.3 (V_{CC}), TMR52.3 (V_{CC}), TMR53.3 (V_{CC}), TMR54.3 (V_{CC}), TMR55.3 (V_{CC}), TMR56.3 (V_{CC}), TMR57.3 (V_{CC}), TMR58.3 (V_{CC}), TMR59.3 (V_{CC}), TMR60.3 (V_{CC}), TMR61.3 (V_{CC}), TMR62.3 (V_{CC}), TMR63.3 (V_{CC}), TMR64.3 (V_{CC}), TMR65.3 (V_{CC}), TMR66.3 (V_{CC}), TMR67.3 (V_{CC}), TMR68.3 (V_{CC}), TMR69.3 (V_{CC}), TMR70.3 (V_{CC}), TMR71.3 (V_{CC}), TMR72.3 (V_{CC}); also elsewhere on the board

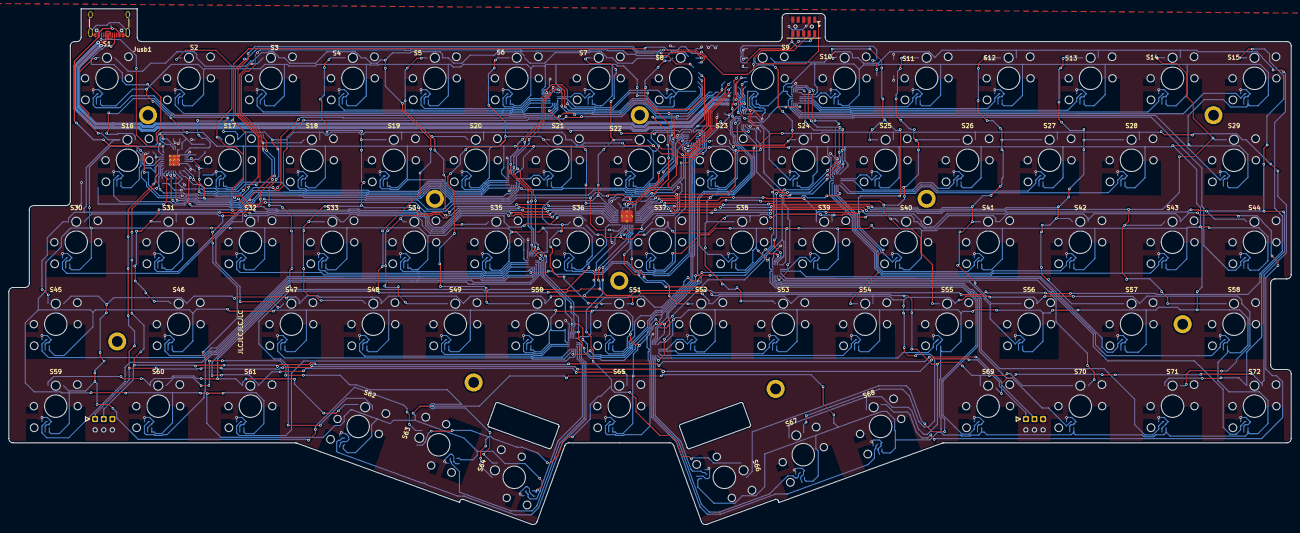
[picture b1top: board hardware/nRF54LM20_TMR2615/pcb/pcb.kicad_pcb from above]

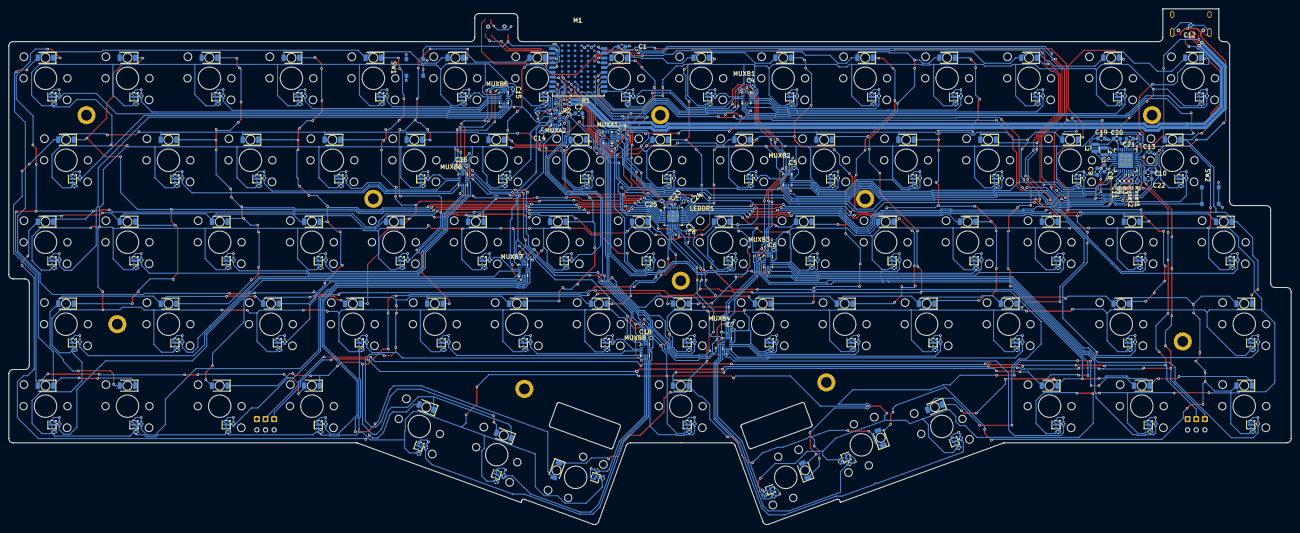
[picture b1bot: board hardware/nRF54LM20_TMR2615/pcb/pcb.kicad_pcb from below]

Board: 2 copper layers, 297.2 x 119.5 mm, 426 parts (337 on the bottom side), 144 nets.
